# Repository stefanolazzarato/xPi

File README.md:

# xPi
Raspberry Pi expansion board

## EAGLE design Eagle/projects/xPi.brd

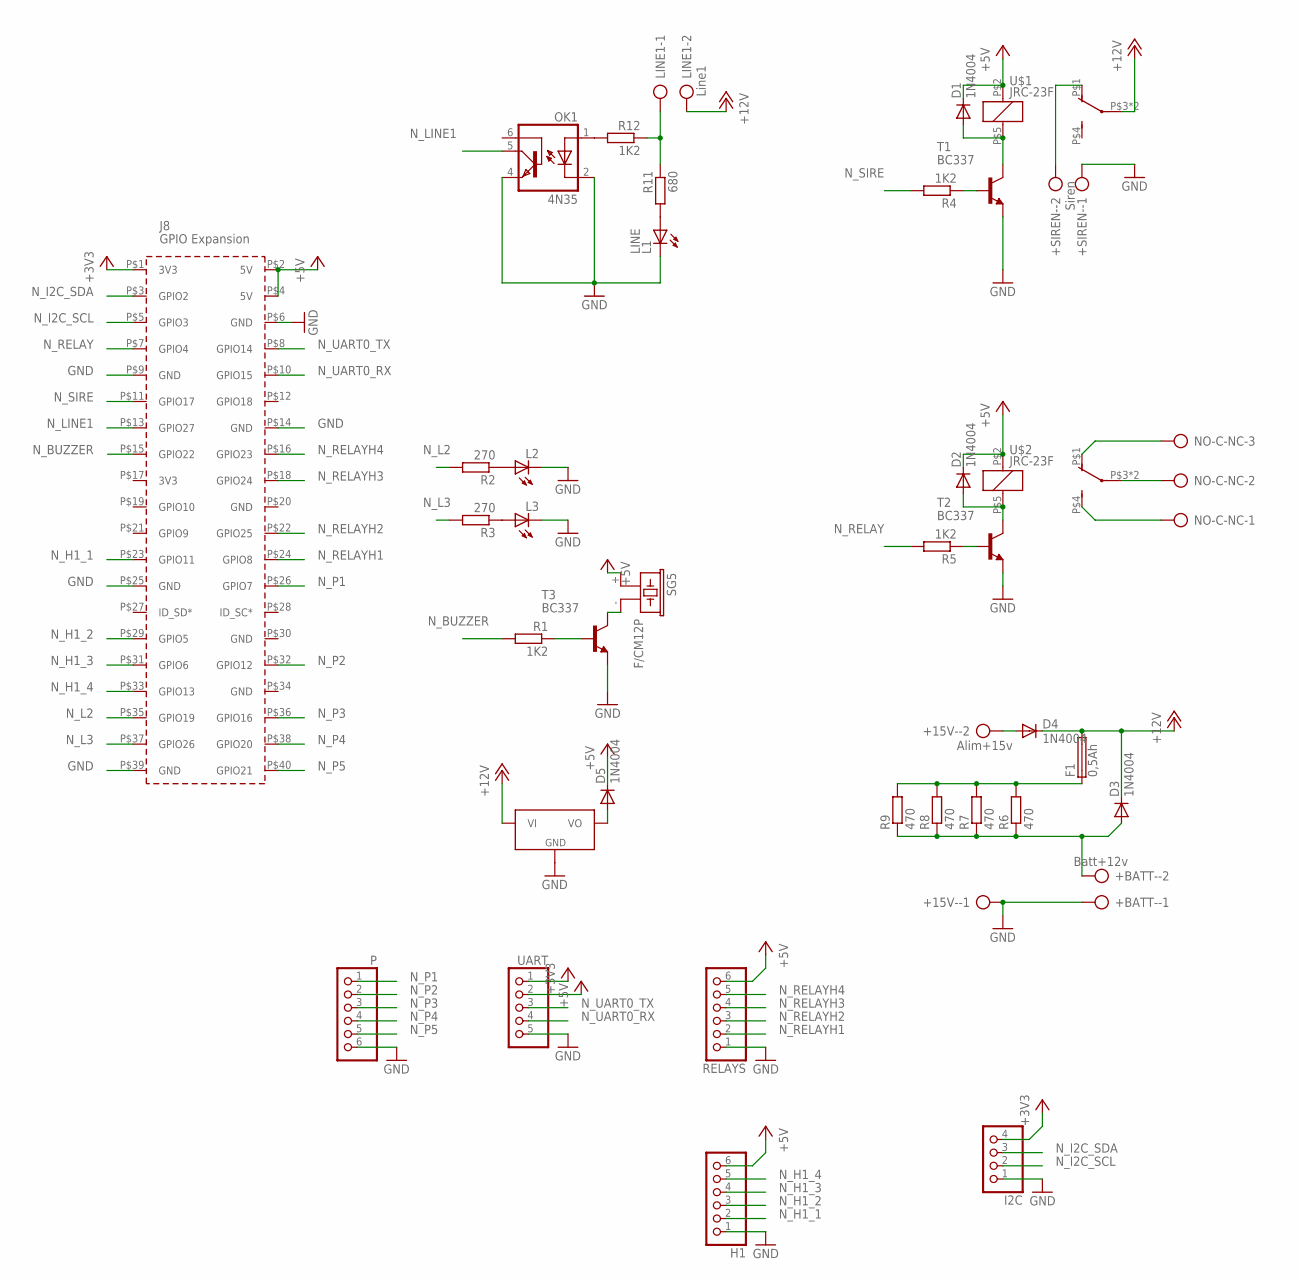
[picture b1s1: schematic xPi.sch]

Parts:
+15V-: Alim+15v; AK300/2
+BATT-: Batt+12v; AK300/2
+SIREN-: Siren; AK300/2
D1, D2, D3, D4, D5: 1N4004; DO41-10
F1: 0,5Ah; KS9V
H1: PINHD-1X6; 1X06
I2C: PINHD-1X4; 1X04
L1: LINE; LED3MM
L2, L3: LED3MM
LINE1: Line1; AK300/2
NO-C-NC: AK300/3
OK1: 4N35; DIL06
P: PINHD-1X6; 1X06
R1, R12: 1K2; 0204/7
R2, R3: 270; 0204/7
R4, R5: 1K2; 0204V
R6, R7, R8, R9: 470; 0204/7
R11: 680; 0204/7
RELAYS: PINHD-1X6; 1X06
SG5: F/CM12P
T1, T2, T3: BC337; TO92
U$1, U$2: JRC-23F
U$5: DSWY2596
U$6: RPI3_2
UART: PINHD-1X5; 1X05

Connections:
+3V3: I2C.4, U$6.P$1 (3V3), UART.1
+5V: D1.C, D2.C, D5.C, H1.6, RELAYS.6, SG5.+ (1), U$1.P$2 (1), U$2.P$2 (1), U$6.P$2 (5V), U$6.P$4 (5V), UART.2
+12V: D3.C, D4.C, F1.2, LINE1.2, U$1.P$3, U$1.P$6, U$5.VI
GND: +15V-.1, +BATT-.1, +SIREN-.1, H1.1, I2C.1, L1.K (C), L2.K (C), L3.K (C), OK1.2 (C), OK1.4 (EMI), P.6, RELAYS.1, T1.1 (E), T2.1 (E), T3.1 (E), U$5.GNDI (GND), U$5.GNDO (GND), U$6.P$6 (GND), U$6.P$9 (GND), U$6.P$14 (GND), U$6.P$25 (GND), U$6.P$39 (GND), UART.5
unnamed: LINE1.1, R11.1, R12.1
unnamed: OK1.1 (A), R12.2
unnamed: R5.1, T2.2 (B)
unnamed: SG5.- (2), T3.3 (C)
unnamed: NO-C-NC.1, U$2.P$4 (S)
unnamed: L2.A, R2.1
unnamed: R4.1, T1.2 (B)
unnamed: +15V-.2, D4.A
unnamed: D5.A, U$5.VO
unnamed: R1.1, T3.2 (B)
unnamed: +SIREN-.2, U$1.P$1 (O)
unnamed: +BATT-.2, D3.A, R6.1, R7.1, R8.1, R9.1
unnamed: NO-C-NC.3, U$2.P$1 (O)
unnamed: NO-C-NC.2, U$2.P$3, U$2.P$6
unnamed: D2.A, T2.3 (C), U$2.P$5 (2)
unnamed: F1.1, R6.2, R7.2, R8.2, R9.2
unnamed: D1.A, T1.3 (C), U$1.P$5 (2)
unnamed: L1.A, R11.2
unnamed: L3.A, R3.1
N_BUZZER: R1.2, U$6.P$15 (GPIO22)
N_H1_1: H1.2, U$6.P$23 (GPIO11)
N_H1_2: H1.3, U$6.P$29 (GPIO5)
N_H1_3: H1.4, U$6.P$31 (GPIO6)
N_H1_4: H1.5, U$6.P$33 (GPIO13)
N_I2C_SCL: I2C.2, U$6.P$5 (GPIO3)
N_I2C_SDA: I2C.3, U$6.P$3 (GPIO2)
N_L2: R2.2, U$6.P$35 (GPIO19)
N_L3: R3.2, U$6.P$37 (GPIO26)
N_LINE1: OK1.5 (COL), U$6.P$13 (GPIO27)
N_P1: P.1, U$6.P$26 (GPIO7)
N_P2: P.2, U$6.P$32 (GPIO12)
N_P3: P.3, U$6.P$36 (GPIO16)
N_P4: P.4, U$6.P$38 (GPIO20)
N_P5: P.5, U$6.P$40 (GPIO21)
N_RELAY: R5.2, U$6.P$7 (GPIO4)
N_RELAYH1: RELAYS.2, U$6.P$24 (GPIO8)
N_RELAYH2: RELAYS.3, U$6.P$22 (GPIO25)
N_RELAYH3: RELAYS.4, U$6.P$18 (GPIO24)
N_RELAYH4: RELAYS.5, U$6.P$16 (GPIO23)
N_SIRE: R4.2, U$6.P$11 (GPIO17)
N_UART0_RX: U$6.P$10 (GPIO15), UART.4
N_UART0_TX: U$6.P$8 (GPIO14), UART.3

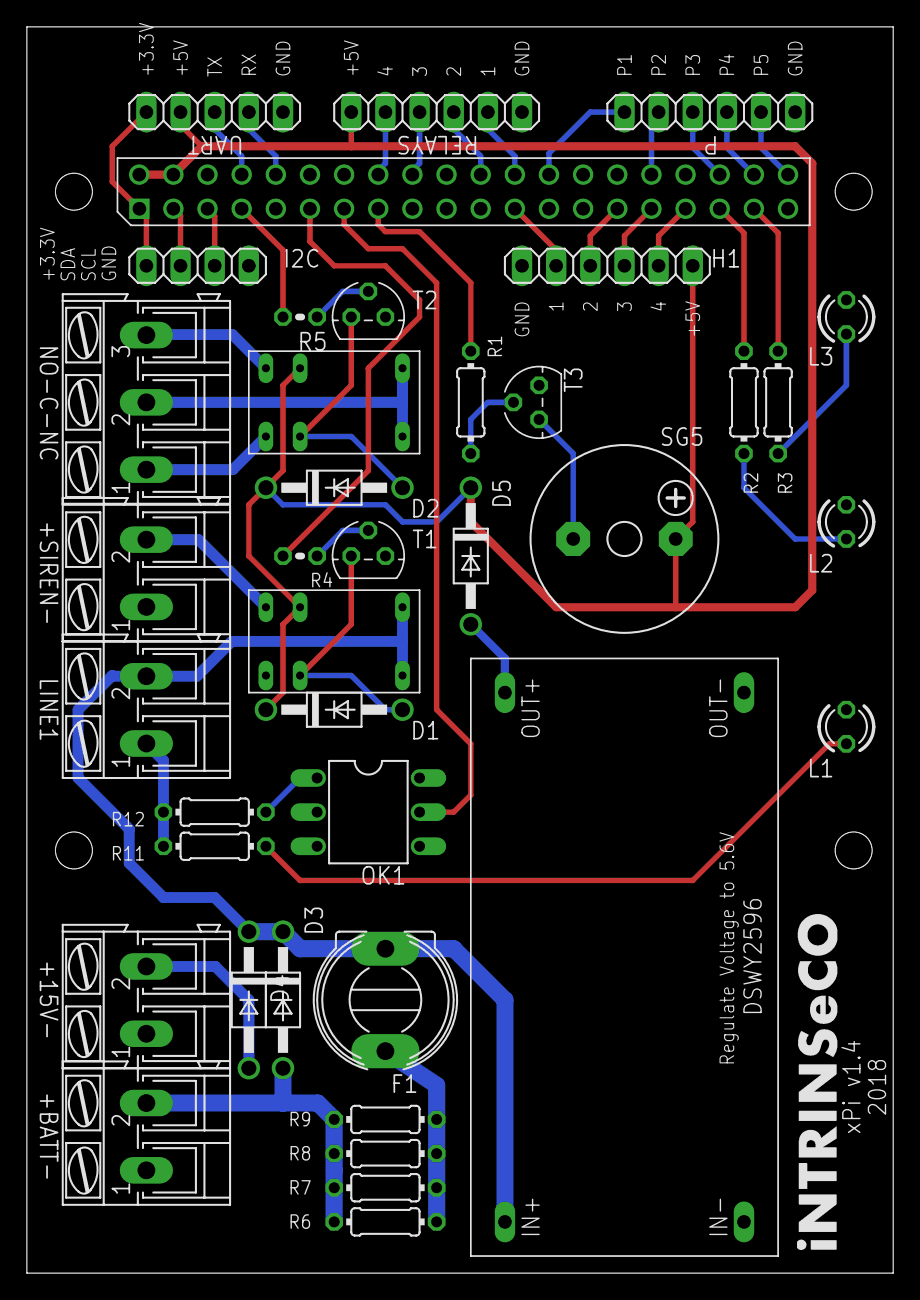
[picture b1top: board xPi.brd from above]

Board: 2 copper layers, 64.4 x 92.7 mm, 39 parts (0 on the bottom side), 46 nets.

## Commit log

2018-04-16 Add xPi v1.3; add libraries as submodule.
2018-05-08 xPi v1.4
